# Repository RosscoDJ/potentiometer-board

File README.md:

# potentiometer-board
Potentiometer board for 8x potentiometers, includes switches for signal/vcc/gnd connections to A and B terminals per pot, as well as Vcc and Gnd connections to board.

>> Kicad files with schematic and PCB layout.
>> Gerber files in Pot_Board_REVA folder.

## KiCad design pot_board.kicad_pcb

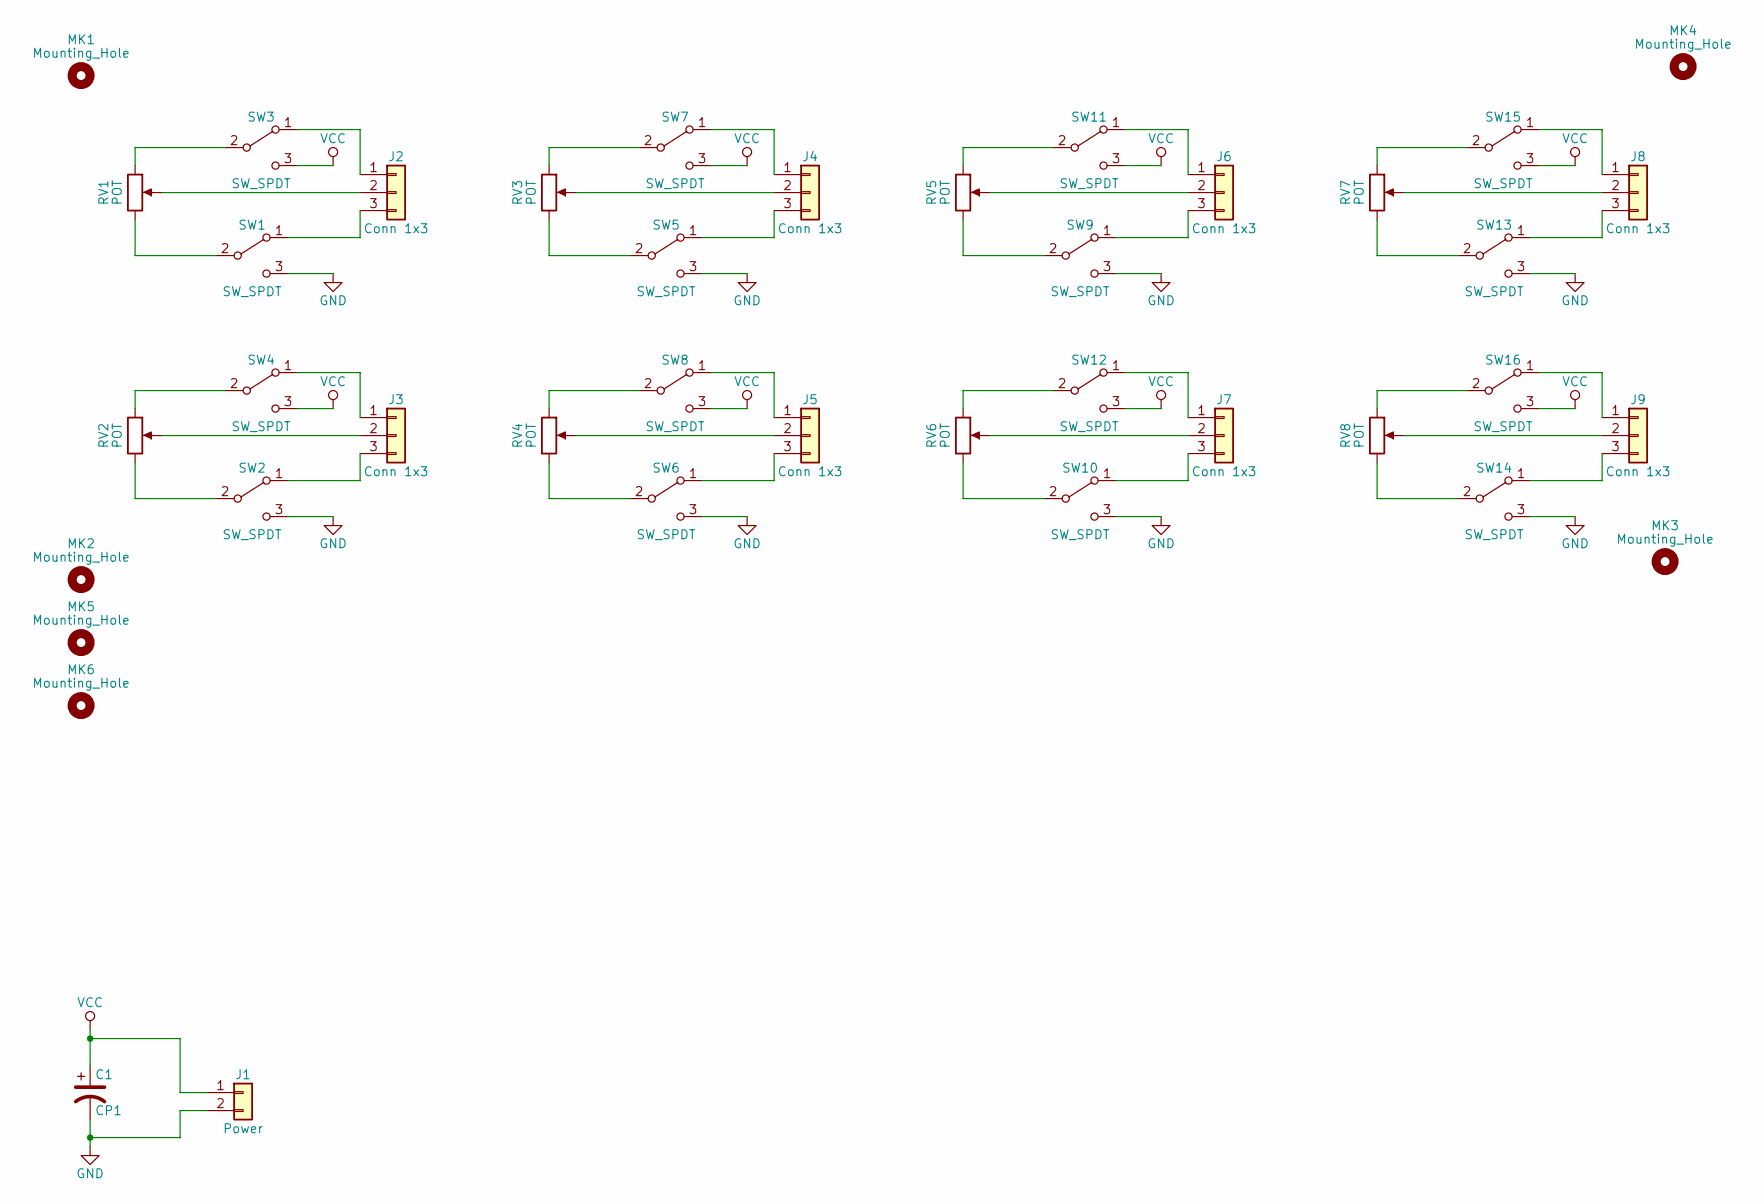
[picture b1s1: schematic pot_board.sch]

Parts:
C1: CP1; CP_Radial_D5.0mm_P2.00mm
J1: Power; Socket_Strip_Straight_1x02_Pitch2.54mm
J2, J3, J4, J5, J6, J7, J8, J9: Conn 1x3; Socket_Strip_Straight_1x03_Pitch2.54mm
MK1, MK2, MK3, MK4, MK5, MK6: Mounting_Hole; MountingHole_3.2mm_M3
RV1, RV2, RV3, RV4, RV5, RV6, RV7, RV8: POT; Potentiometer_Bourns_PTV09A-1_Horizontal
SW1, SW2, SW3, SW4, SW5, SW6, SW7, SW8, SW9, SW10, SW11, SW12, SW13, SW14, SW15, SW16: SW_SPDT; SW_OS102011MS2QN1

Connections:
GND: C1.2, J1.2, SW1.3 (C), SW2.3 (C), SW5.3 (C), SW6.3 (C), SW9.3 (C), SW10.3 (C), SW13.3 (C), SW14.3 (C)
unnamed: J2.1, SW3.1 (A)
unnamed: J2.2, RV1.2
unnamed: J2.3, SW1.1 (A)
unnamed: J3.1, SW4.1 (A)
unnamed: J3.2, RV2.2
unnamed: J3.3, SW2.1 (A)
unnamed: J4.1, SW7.1 (A)
unnamed: J4.2, RV3.2
unnamed: J4.3, SW5.1 (A)
unnamed: J5.1, SW8.1 (A)
unnamed: J5.2, RV4.2
unnamed: J5.3, SW6.1 (A)
unnamed: J6.1, SW11.1 (A)
unnamed: J6.2, RV5.2
unnamed: J6.3, SW9.1 (A)
unnamed: J7.1, SW12.1 (A)
unnamed: J7.2, RV6.2
unnamed: J7.3, SW10.1 (A)
unnamed: J8.1, SW15.1 (A)
unnamed: J8.2, RV7.2
unnamed: J8.3, SW13.1 (A)
unnamed: J9.1, SW16.1 (A)
unnamed: J9.2, RV8.2
unnamed: J9.3, SW14.1 (A)
unnamed: RV1.1, SW3.2 (B)
unnamed: RV1.3, SW1.2 (B)
unnamed: RV2.1, SW4.2 (B)
unnamed: RV2.3, SW2.2 (B)
unnamed: RV3.1, SW7.2 (B)
unnamed: RV3.3, SW5.2 (B)
unnamed: RV4.1, SW8.2 (B)
unnamed: RV4.3, SW6.2 (B)
unnamed: RV5.1, SW11.2 (B)
unnamed: RV5.3, SW9.2 (B)
unnamed: RV6.1, SW12.2 (B)
unnamed: RV6.3, SW10.2 (B)
unnamed: RV7.1, SW15.2 (B)
unnamed: RV7.3, SW13.2 (B)
unnamed: RV8.1, SW16.2 (B)
unnamed: RV8.3, SW14.2 (B)
VCC: C1.1, J1.1, SW3.3 (C), SW4.3 (C), SW7.3 (C), SW8.3 (C), SW11.3 (C), SW12.3 (C), SW15.3 (C), SW16.3 (C)

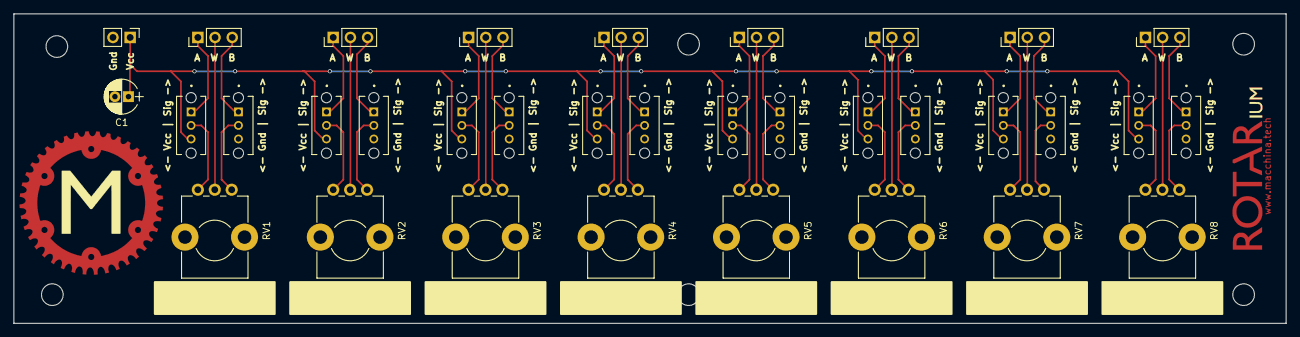
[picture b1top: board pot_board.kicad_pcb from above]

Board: 2 copper layers, 188.0 x 45.7 mm, 40 parts (0 on the bottom side), 42 nets.

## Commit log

2018-05-08 Add files via upload
    Add kicad files for project. Rev A.
2018-05-08 Add files via upload
    Gerber files for REV. A board
2018-05-08 Update README.md
    Add description of files, as well as Gerber file folder.
2018-05-21 Add files via upload
    Backup of all local files prior to re-layout of PCB
2018-05-21 Add files via upload
    Re-work PCB layout with more accurate spacings for components.
    Add Mecchina artwork to PCB.
2018-05-21 Add files via upload
    Move switches to more ergonomic position.

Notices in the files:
pot_board.kicad_pcb:
© Mecchina Tech 2018
